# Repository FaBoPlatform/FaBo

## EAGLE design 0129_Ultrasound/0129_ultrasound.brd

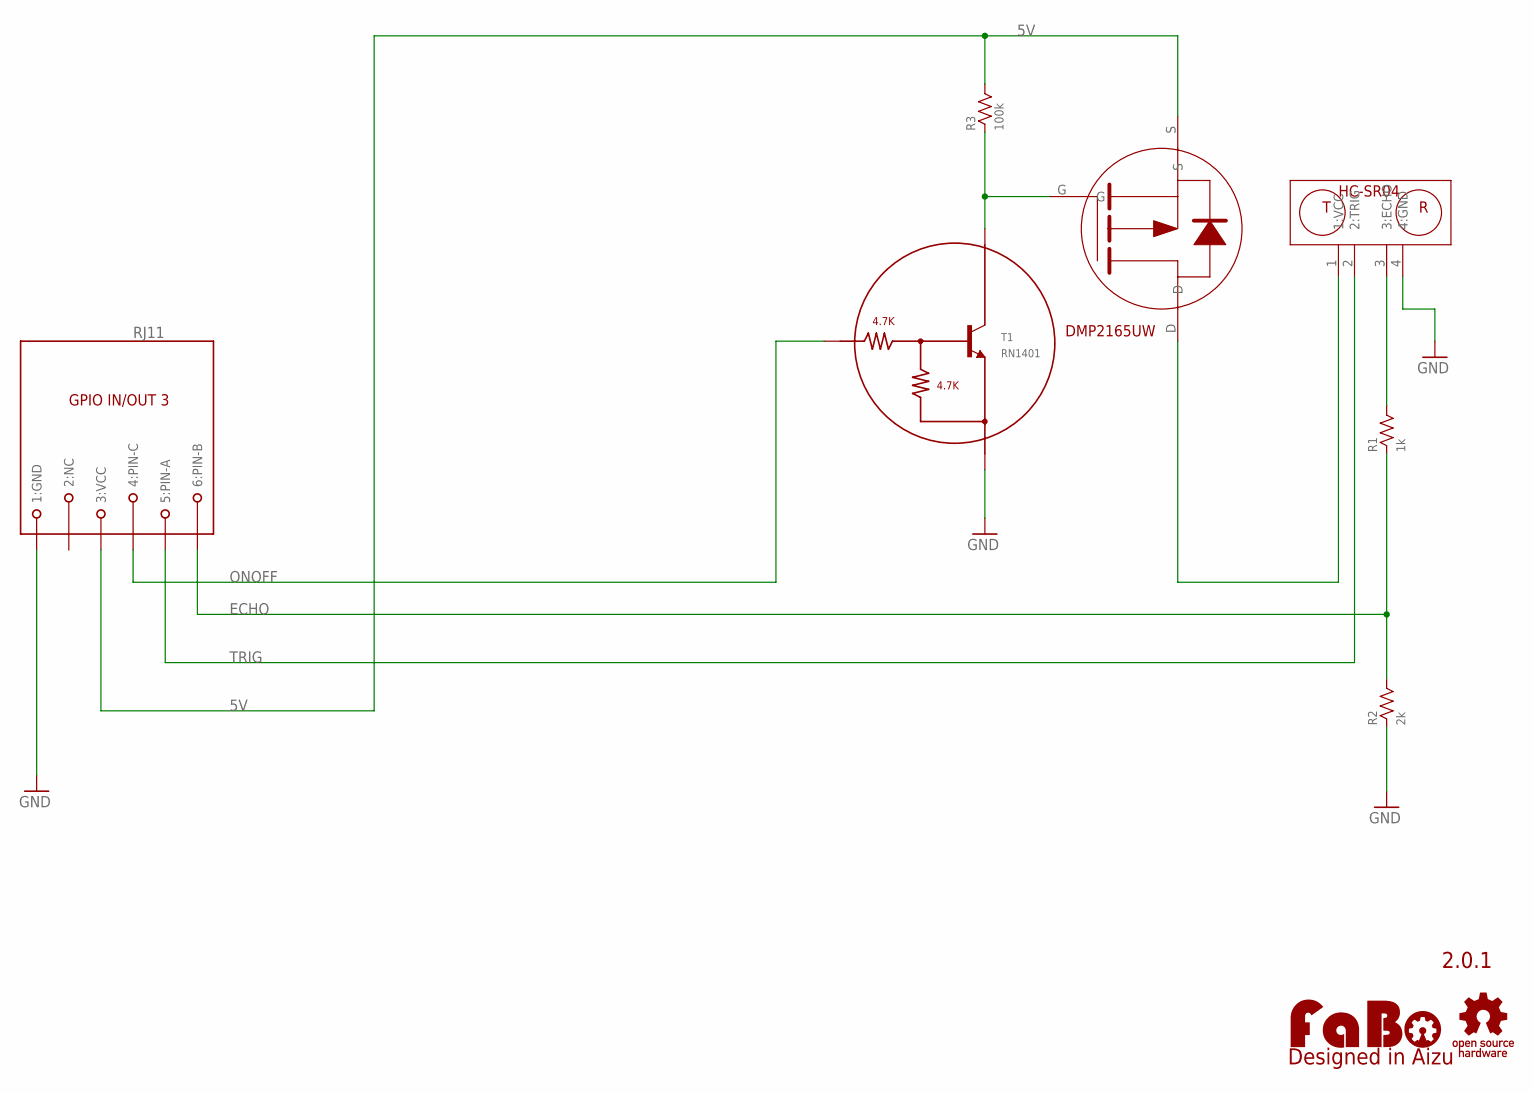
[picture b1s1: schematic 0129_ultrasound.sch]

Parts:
LOGO1: LOGO_FABO-M_BOTTOM; LOGO_FABO_M_BOTTOM
PFET: DMP2165UW; DMP2165_SOT323
R1: 1k; 0603-NARROW
R2: 2k; 0603-NARROW
R3: 100k; 0603-NARROW
RJ11: MODULAR-JACK-6P-RJ11_GPIO3; 7002-6PXC-X
T1: RN1401; SC-59
U$3: LOGO_OSHW-M_BOTTOM; LOGO_OSHW_M_BOTTOM
U$5: HC-SR04

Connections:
5V: PFET.S, R3.2, RJ11.3 (3:VCC)
ECHO: R1.1, R2.2, RJ11.6 (6:PIN-B)
GND: R2.1, RJ11.1 (1:GND), T1.E, U$5.4 (4:GND)
unnamed: R1.2, U$5.3 (3:ECHO)
unnamed: PFET.D, U$5.1 (1:VCC)
ONOFF: RJ11.4 (4:PIN-C), T1.B
POWERONOFF: PFET.G, R3.1, T1.C
TRIG: RJ11.5 (5:PIN-A), U$5.2 (2:TRIG)

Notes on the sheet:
2.0.1

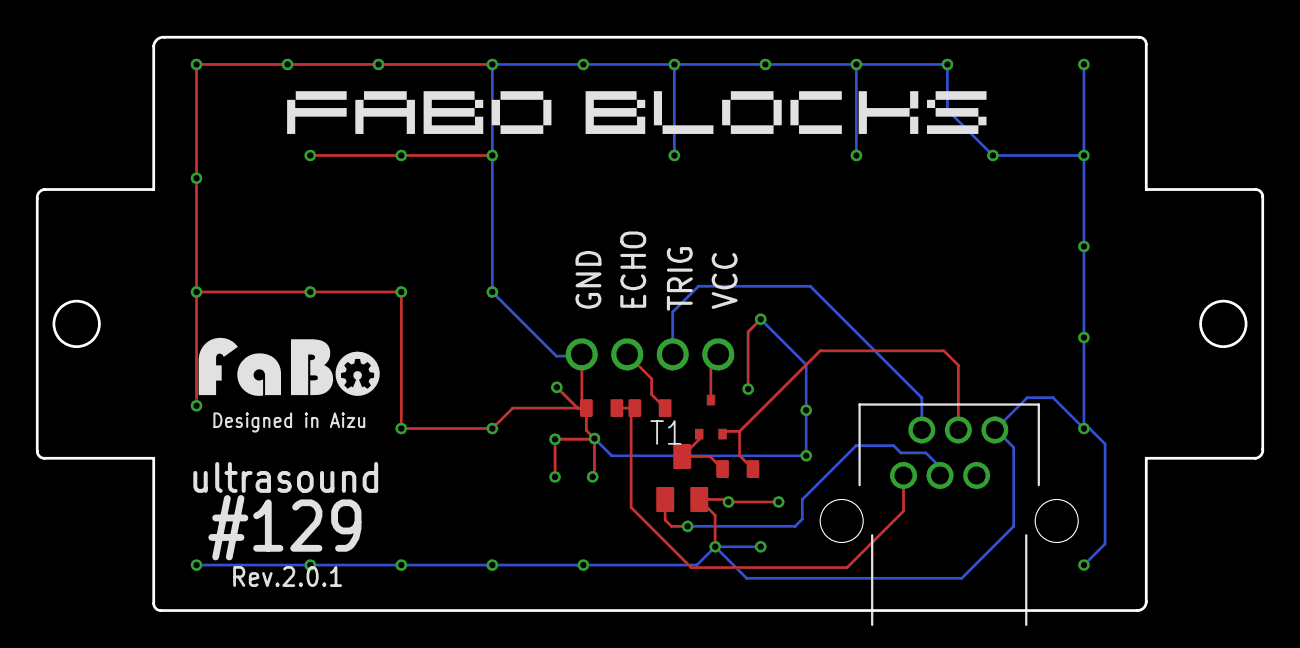
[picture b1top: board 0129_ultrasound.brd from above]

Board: 2 copper layers, 68.4 x 32.0 mm, 11 parts (1 on the bottom side), 8 nets.

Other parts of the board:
U$2, U$4: 4-1BLOCK

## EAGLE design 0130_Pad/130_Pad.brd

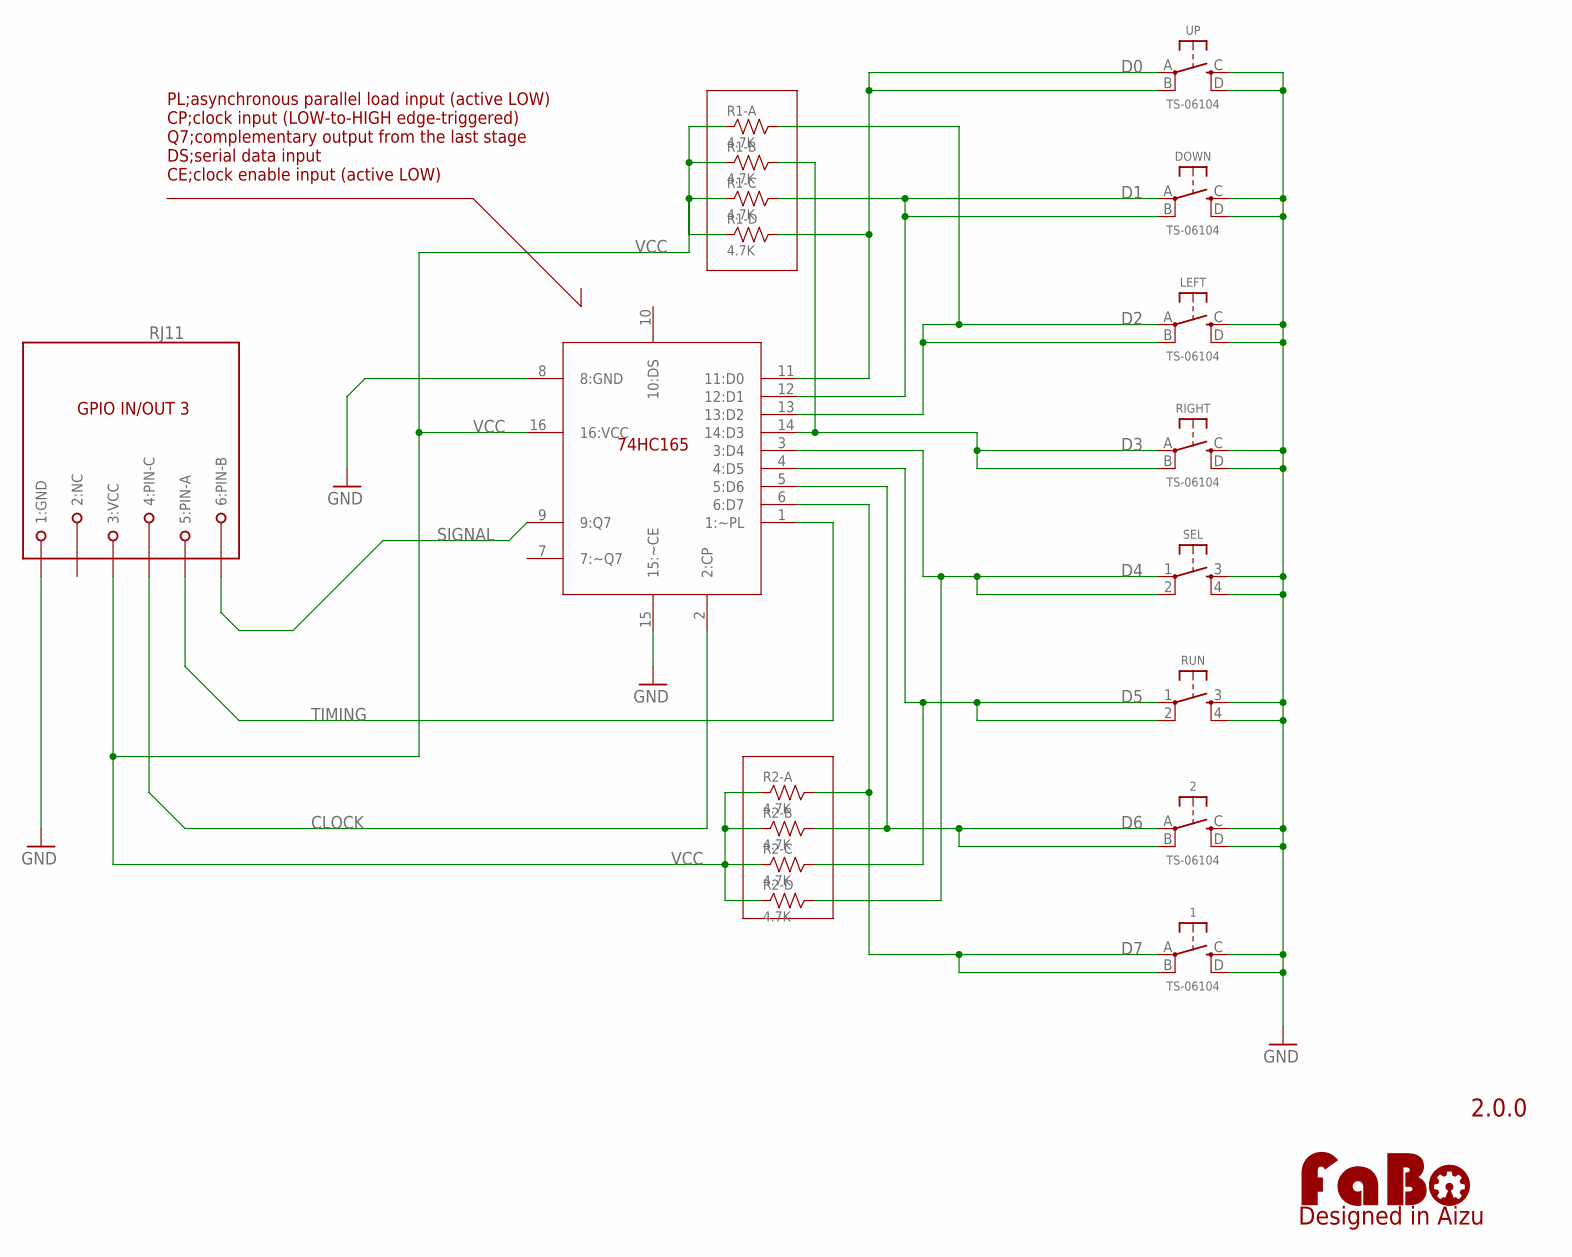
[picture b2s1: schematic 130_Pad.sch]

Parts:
1, 2: TS-06104
DOWN: TS-06104
LEFT: TS-06104
LOGO1: LOGO_FABO-M_BOTTOM; LOGO_FABO_M_BOTTOM
R1, R2: 4.7K; EXBV8V
RIGHT: TS-06104
RJ11: MODULAR-JACK-6P-RJ11_GPIO3; 7002-6PXC-X
RUN: TACT-SWITCH-SMD_KMR2; KMR2
SEL: TACT-SWITCH-SMD_KMR2; KMR2
U$5: 74HC165; SO16
UP: TS-06104

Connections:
CLOCK: RJ11.4 (4:PIN-C), U$5.2 (2:CP)
D0: R1.5 (2), U$5.11 (11:D0), UP.A, UP.B
D1: DOWN.A, DOWN.B, R1.6 (2), U$5.12 (12:D1)
D2: LEFT.A, LEFT.B, R1.8 (2), U$5.13 (13:D2)
D3: R1.7 (2), RIGHT.A, RIGHT.B, U$5.14 (14:D3)
D4: R2.5 (2), SEL.1, SEL.2, U$5.3 (3:D4)
D5: R2.6 (2), RUN.1, RUN.2, U$5.4 (4:D5)
D6: 2.A, 2.B, R2.7 (2), U$5.5 (5:D6)
D7: 1.A, 1.B, R2.8 (2), U$5.6 (6:D7)
GND: 1.C, 1.D, 2.C, 2.D, DOWN.C, DOWN.D, LEFT.C, LEFT.D, RIGHT.C, RIGHT.D, RJ11.1 (1:GND), RUN.3, RUN.4, SEL.3, SEL.4, U$5.8 (8:GND), U$5.15 (15:~CE), UP.C, UP.D
SIGNAL: RJ11.6 (6:PIN-B), U$5.9 (9:Q7)
TIMING: RJ11.5 (5:PIN-A), U$5.1 (1:~PL)
VCC: R1.1, R1.2 (1), R1.3 (1), R1.4 (1), R2.1, R2.2 (1), R2.3 (1), R2.4 (1), RJ11.3 (3:VCC), U$5.16 (16:VCC)

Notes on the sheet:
2.0.0
PL;asynchronous parallel load input (active LOW) CP;clock input (LOW-to-HIGH edge-triggered) Q7;complementary output from the last stage DS;serial data input CE;clock enable input (active LOW)

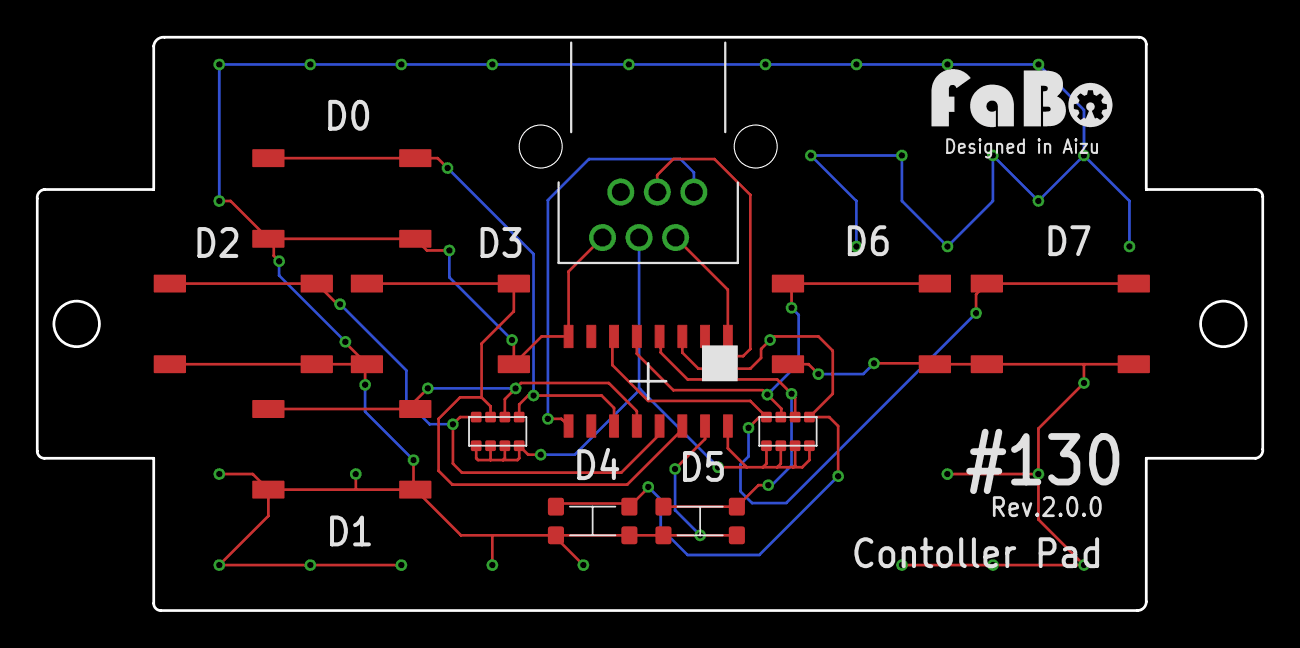
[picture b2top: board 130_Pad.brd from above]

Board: 2 copper layers, 68.4 x 32.0 mm, 15 parts (1 on the bottom side), 13 nets.

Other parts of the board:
U$2, U$4: 4-1BLOCK

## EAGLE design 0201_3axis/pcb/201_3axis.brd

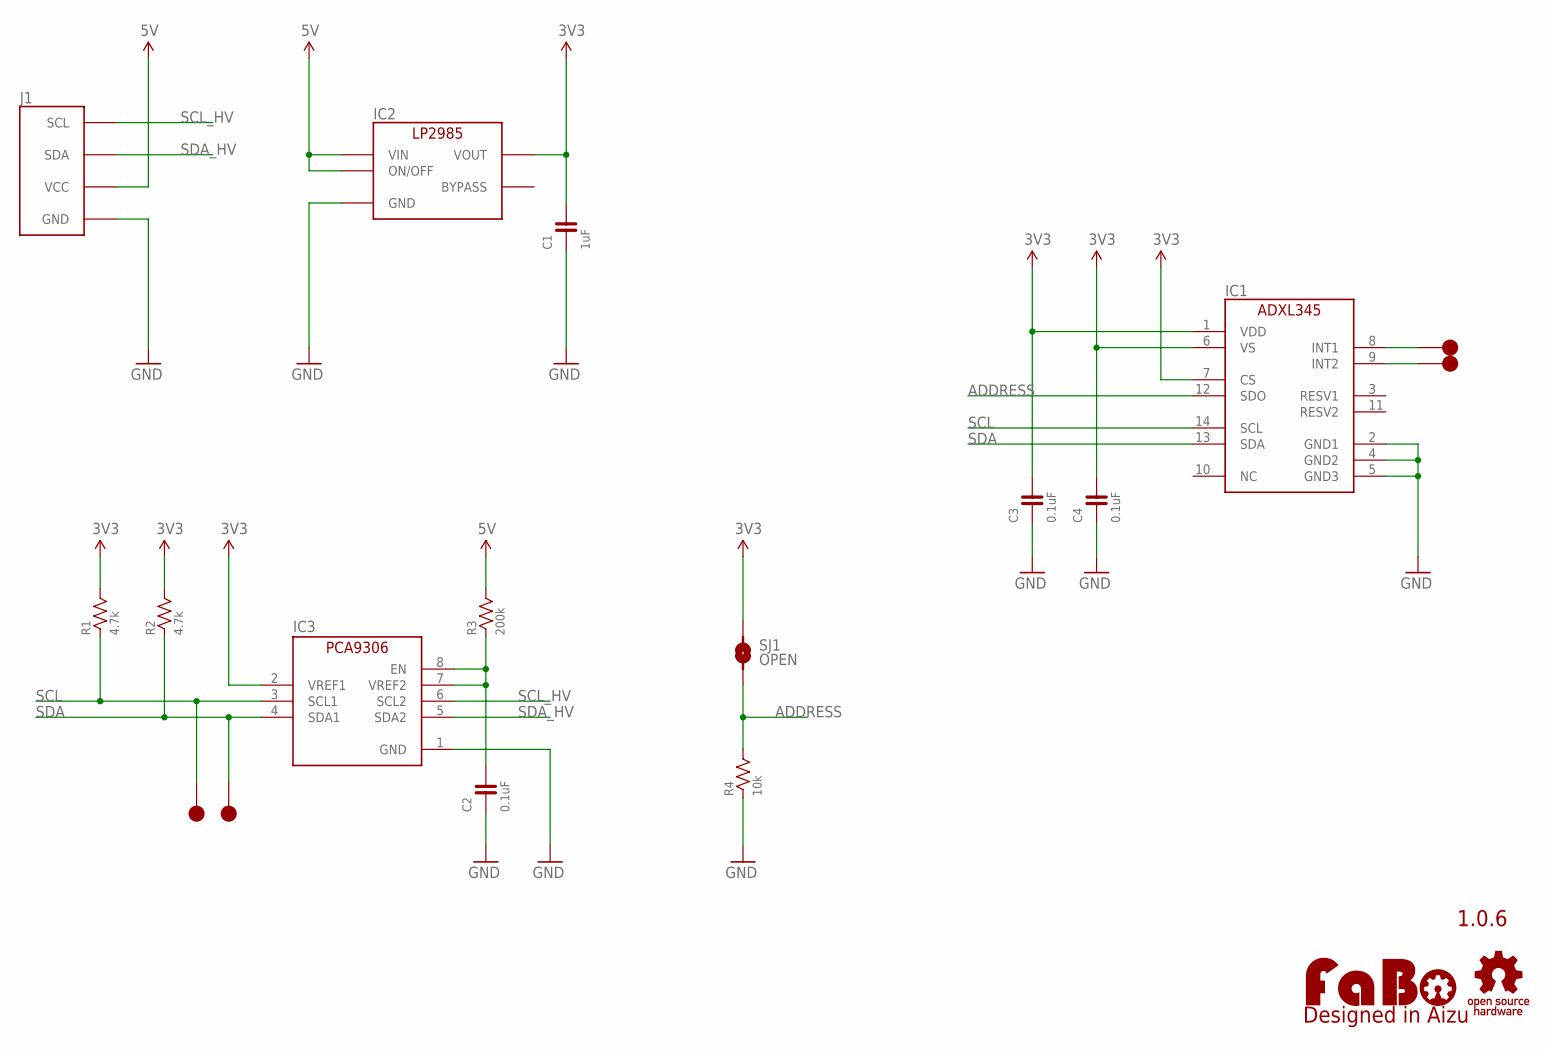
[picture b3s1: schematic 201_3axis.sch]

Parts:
C1: 1uF; 0603
C2, C3, C4: 0.1uF; 0603
IC1: AD-ADXL345; ANALOGDEVICES-ADXL345
IC2: LP2985-33DBV; SOT-23-5
IC3: PCA9306GM; XQFN8
J1: FABO_BRICK_I2C
LOGO1: LOGO_FABO-M; LOGO_FABO_M
R1, R2: 4.7k; 0603
R3: 200k; 0603
R4: 10k; 0603
SJ1: OPEN; SMD-JUMPER-2
TP1, TP2, TP3, TP4: TP-15
U$2: LOGO_OSHW-M_BOTTOM; LOGO_OSHW_M_BOTTOM

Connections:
3V3: C1.2, C3.2, C4.2, IC1.1 (VDD), IC1.6 (VS), IC1.7 (CS), IC2.5 (VOUT), IC3.2 (VREF1), R1.2, R2.2, SJ1.1
5V: IC2.1 (VIN), IC2.3 (ON/OFF), J1.VCC, R3.2
ADDRESS: IC1.12 (SDO), R4.2, SJ1.2
GND: C1.1, C2.1, C3.1, C4.1, IC1.2 (GND1), IC1.4 (GND2), IC1.5 (GND3), IC2.2 (GND), IC3.1 (GND), J1.GND, R4.1
unnamed: C2.2, IC3.7 (VREF2), IC3.8 (EN), R3.1
unnamed: IC1.8 (INT1), TP3.1
unnamed: IC1.9 (INT2), TP4.1
SCL: IC1.14 (SCL), IC3.3 (SCL1), R1.1, TP2.1
SCL_HV: IC3.6 (SCL2), J1.SCL
SDA: IC1.13 (SDA), IC3.4 (SDA1), R2.1, TP1.1
SDA_HV: IC3.5 (SDA2), J1.SDA

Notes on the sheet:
1.0.6

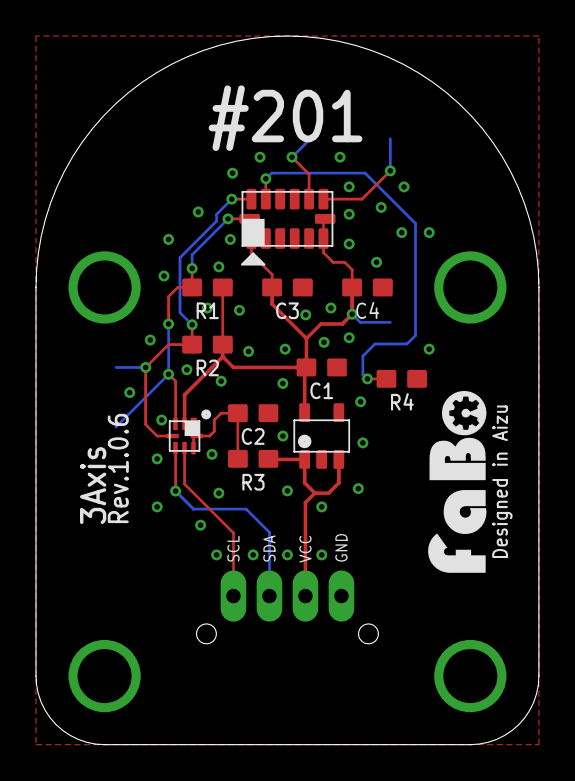
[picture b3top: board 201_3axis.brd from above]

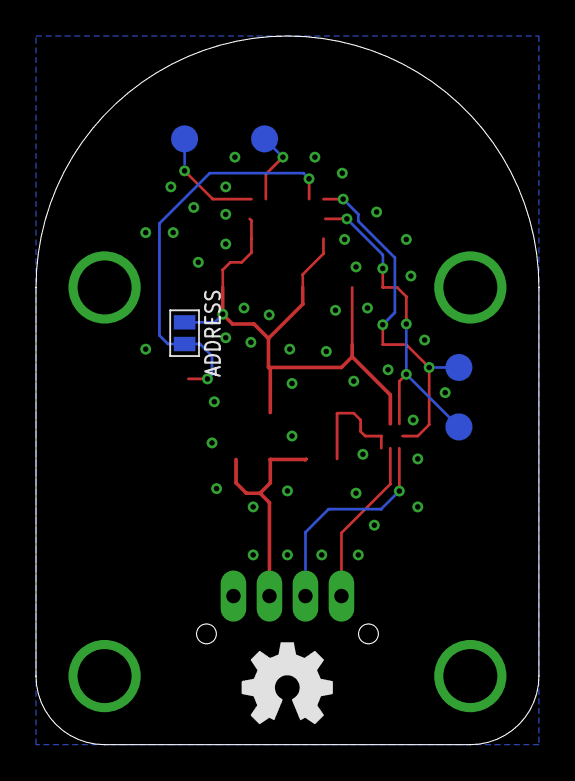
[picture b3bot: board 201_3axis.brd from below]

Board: 2 copper layers, 27.9 x 39.4 mm, 19 parts (5 on the bottom side), 11 nets.

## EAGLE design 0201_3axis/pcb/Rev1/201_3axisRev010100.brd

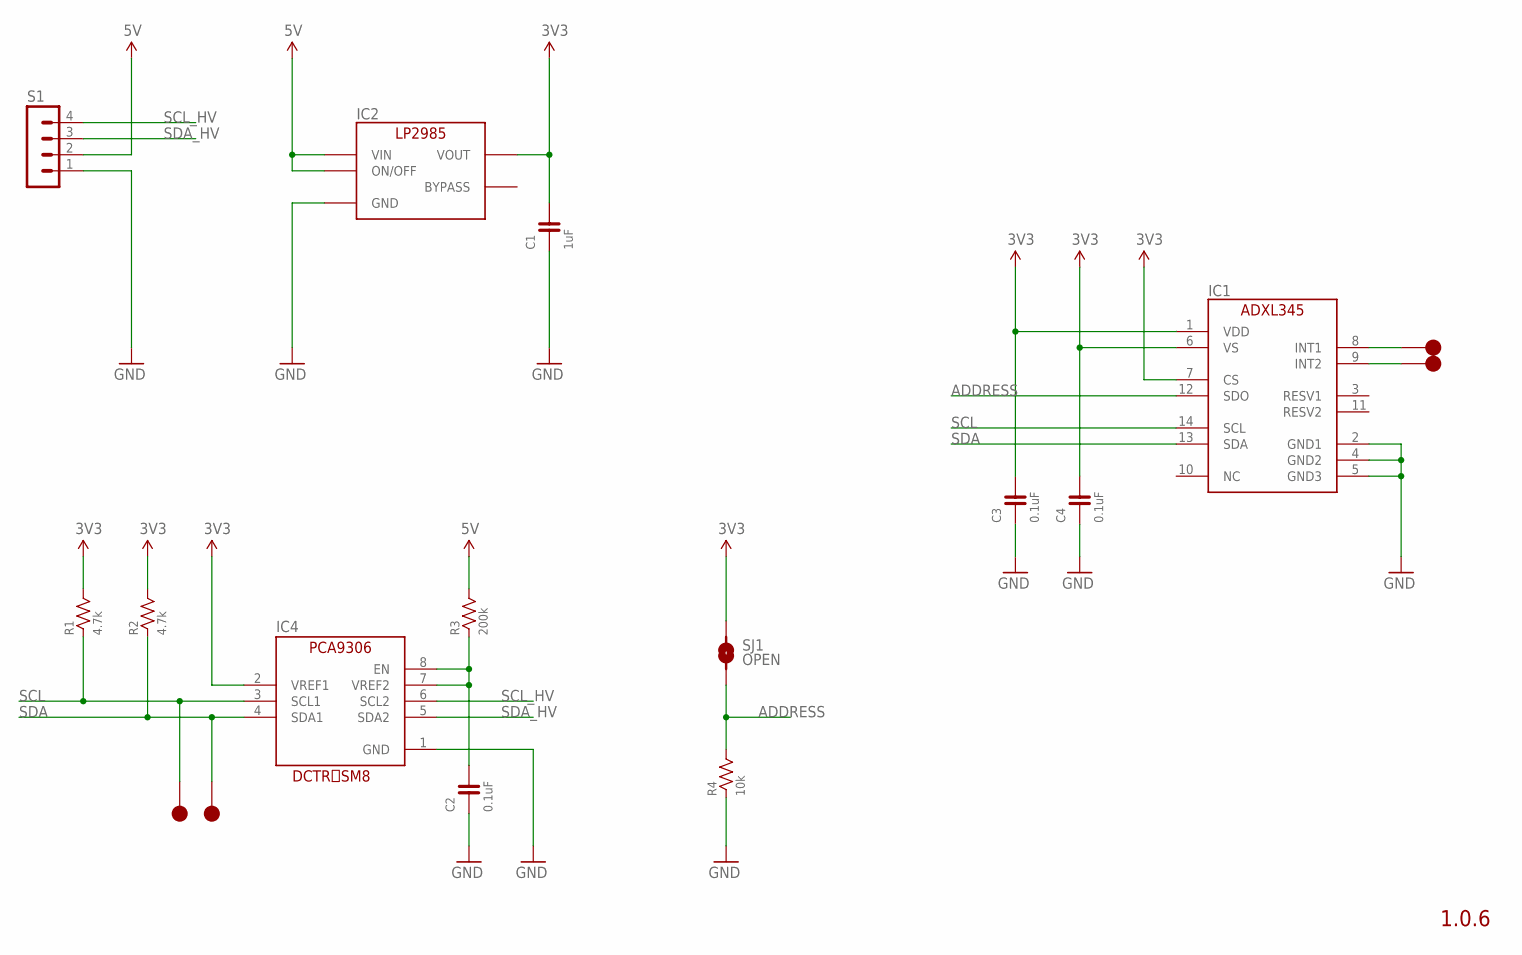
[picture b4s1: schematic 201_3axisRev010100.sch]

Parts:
C1: 1uF; 0603
C2, C3, C4: 0.1uF; 0603
IC1: AD-ADXL345; ANALOGDEVICES-ADXL345
IC2: LP2985-33DBV; SOT-23-5
IC4: PCA9306_SSOP; 8PIN-SSOP
R1, R2: 4.7k; 0603
R3: 200k; 0603
R4: 10k; 0603
S1: MA04-1
SJ1: OPEN; SMD-JUMPER-2
TP1, TP2, TP3, TP4: TP-15

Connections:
3V3: C1.2, C3.2, C4.2, IC1.1 (VDD), IC1.6 (VS), IC1.7 (CS), IC2.5 (VOUT), IC4.2 (VREF1), R1.2, R2.2, SJ1.1
5V: IC2.1 (VIN), IC2.3 (ON/OFF), R3.2, S1.2
ADDRESS: IC1.12 (SDO), R4.2, SJ1.2
GND: C1.1, C2.1, C3.1, C4.1, IC1.2 (GND1), IC1.4 (GND2), IC1.5 (GND3), IC2.2 (GND), IC4.1 (GND), R4.1, S1.1
INT1: IC1.8 (INT1), TP3.1
INT2: IC1.9 (INT2), TP4.1
unnamed: C2.2, IC4.7 (VREF2), IC4.8 (EN), R3.1
SCL: IC1.14 (SCL), IC4.3 (SCL1), R1.1, TP2.1
SCL_HV: IC4.6 (SCL2), S1.4
SDA: IC1.13 (SDA), IC4.4 (SDA1), R2.1, TP1.1
SDA_HV: IC4.5 (SDA2), S1.3

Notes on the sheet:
1.0.6
DCTR SM8

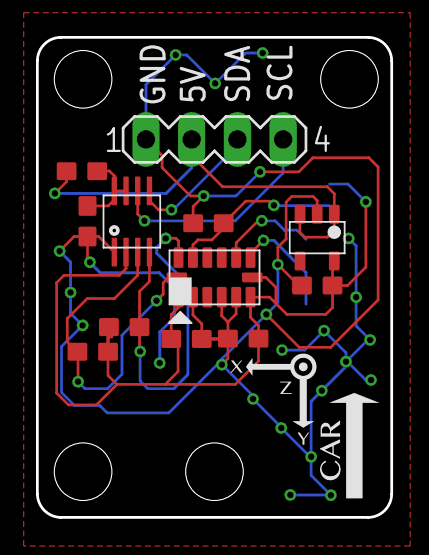
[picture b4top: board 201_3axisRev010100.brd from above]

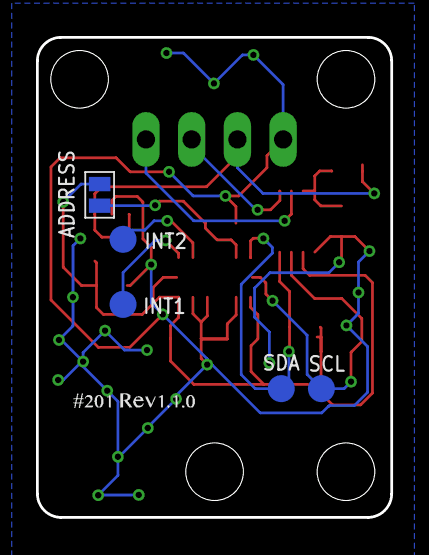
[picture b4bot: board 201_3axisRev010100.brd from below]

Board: 2 copper layers, 19.7 x 26.7 mm, 17 parts (5 on the bottom side), 11 nets.

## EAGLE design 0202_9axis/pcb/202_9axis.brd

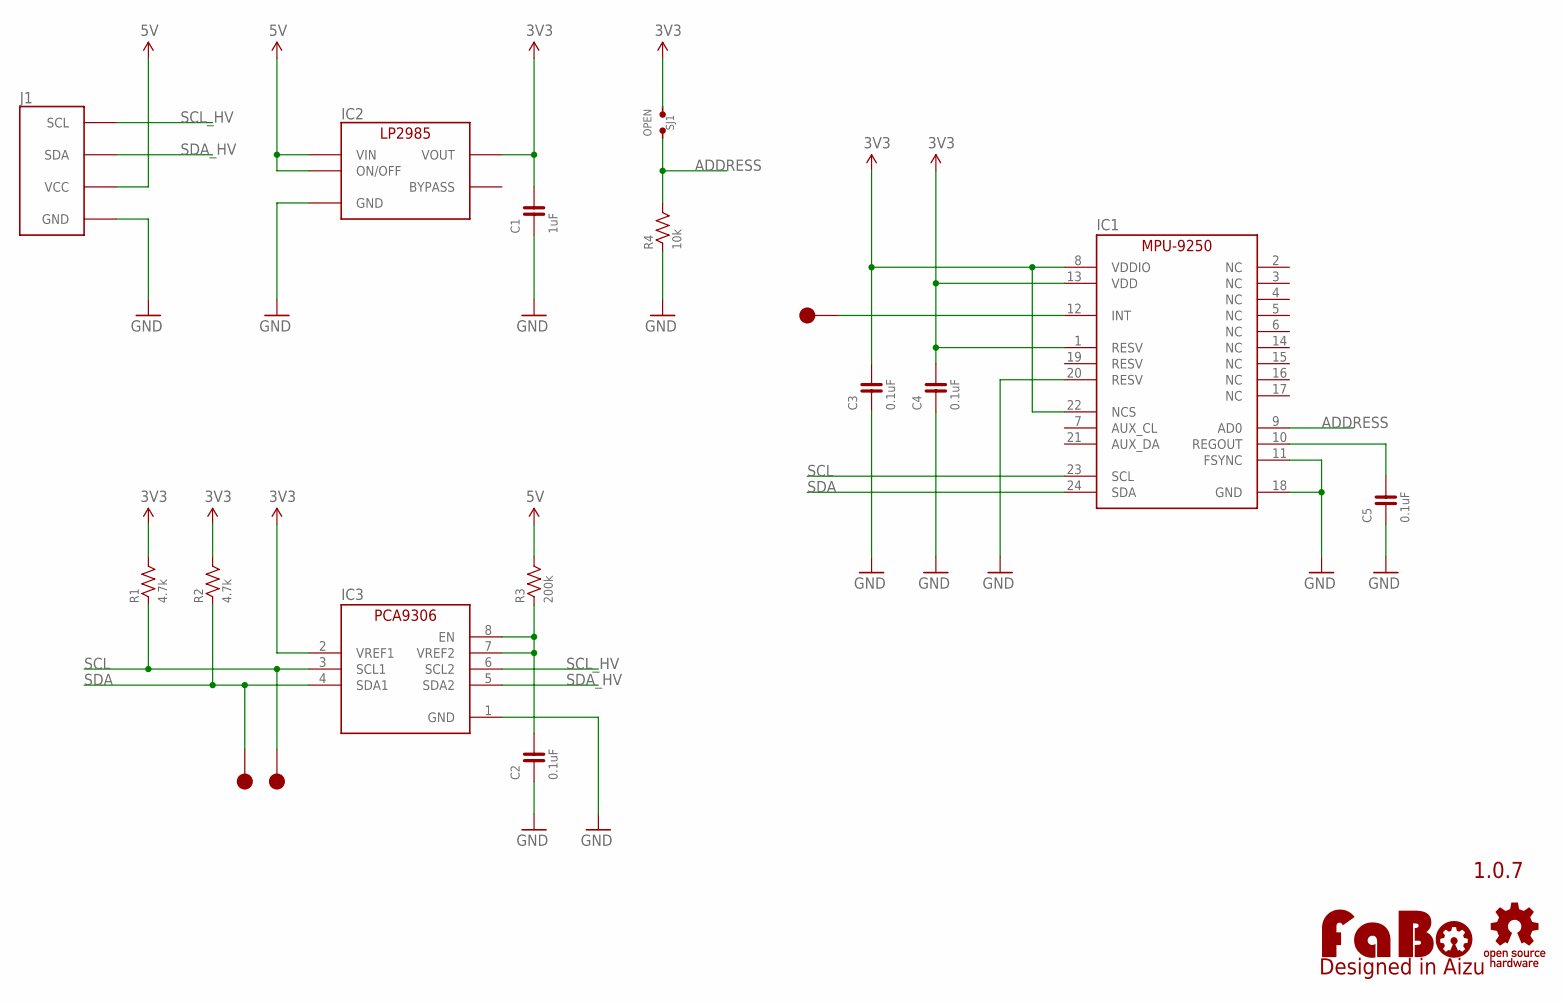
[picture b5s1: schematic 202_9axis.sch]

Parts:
C1: 1uF; 0603
C2, C3, C4, C5: 0.1uF; 0603
IC1: IS-MPU9250; INVENSENSE-MPU9250
IC2: LP2985-33DBV; SOT-23-5
IC3: PCA9306GM; XQFN8
J1: FABO_BRICK_I2C
LOGO1: LOGO_FABO-M; LOGO_FABO_M
R1, R2: 4.7k; 0603
R3: 200k; 0603
R4: 10k; 0603
SJ1: OPEN; SMD-JUMPER-2-OPEN
TP1, TP2, TP3: TP-15
U$2: LOGO_OSHW-M_BOTTOM; LOGO_OSHW_M_BOTTOM

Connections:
3V3: C1.2, C3.2, C4.2, IC1.1 (RESV), IC1.8 (VDDIO), IC1.13 (VDD), IC1.22 (NCS), IC2.5 (VOUT), IC3.2 (VREF1), R1.2, R2.2, SJ1.1
5V: IC2.1 (VIN), IC2.3 (ON/OFF), J1.VCC, R3.2
ADDRESS: IC1.9 (AD0), R4.2, SJ1.2
GND: C1.1, C2.1, C3.1, C4.1, C5.1, IC1.11 (FSYNC), IC1.18 (GND), IC1.20 (RESV), IC2.2 (GND), IC3.1 (GND), J1.GND, R4.1
unnamed: C2.2, IC3.7 (VREF2), IC3.8 (EN), R3.1
unnamed: IC1.12 (INT), TP3.1
REGOUT: C5.2, IC1.10 (REGOUT)
SCL: IC1.23 (SCL), IC3.3 (SCL1), R1.1, TP2.1
SCL_HV: IC3.6 (SCL2), J1.SCL
SDA: IC1.24 (SDA), IC3.4 (SDA1), R2.1, TP1.1
SDA_HV: IC3.5 (SDA2), J1.SDA

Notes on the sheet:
1.0.7

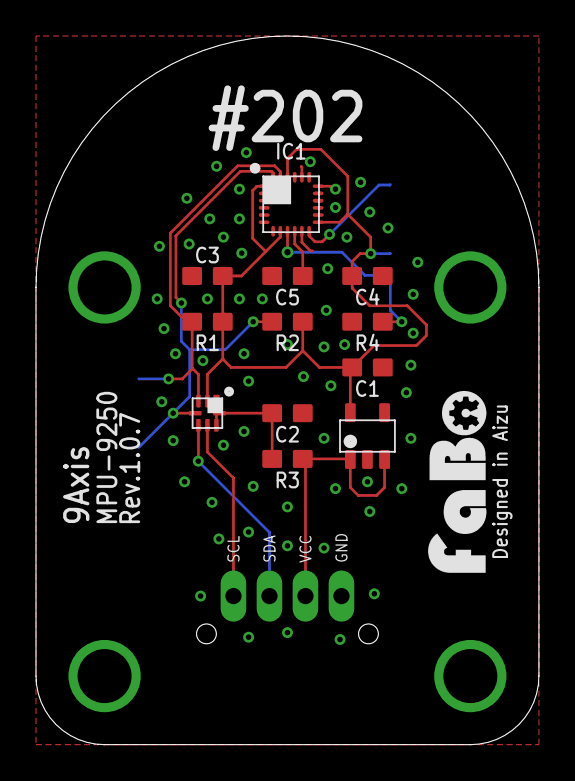
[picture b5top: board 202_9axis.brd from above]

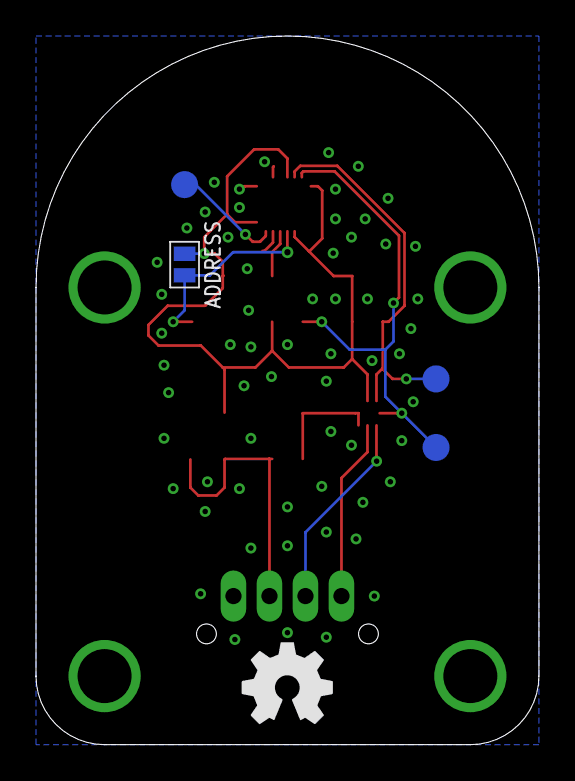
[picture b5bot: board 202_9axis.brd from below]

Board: 2 copper layers, 27.9 x 39.4 mm, 19 parts (4 on the bottom side), 11 nets.

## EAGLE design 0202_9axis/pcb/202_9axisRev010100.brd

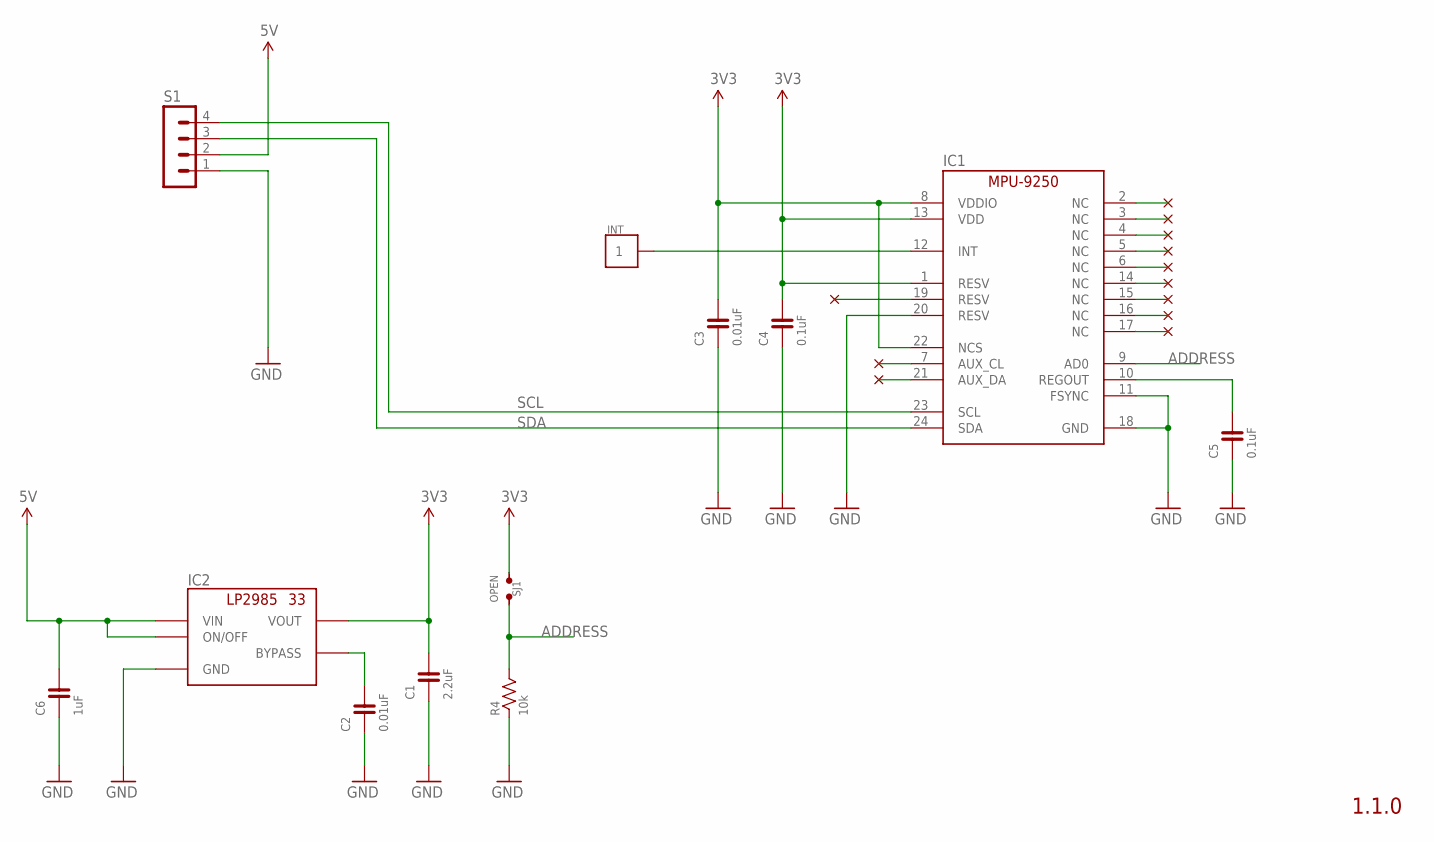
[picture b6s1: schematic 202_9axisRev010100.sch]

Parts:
C1: 2.2uF; 0603
C2, C3: 0.01uF; 0603
C4, C5: 0.1uF; 0603
C6: 1uF; 0603
IC1: IS-MPU9250; INVENSENSE-MPU9250
IC2: LP2985-33DBV; SOT-23-5
INT: PIN_1X1
R4: 10k; 0603
S1: MA04-1
SJ1: OPEN; SMD-JUMPER-2-OPEN

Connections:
3V3: C1.2, C3.2, C4.2, IC1.1 (RESV), IC1.8 (VDDIO), IC1.13 (VDD), IC1.22 (NCS), IC2.5 (VOUT), SJ1.1
5V: C6.2, IC2.1 (VIN), IC2.3 (ON/OFF), S1.2
ADDRESS: IC1.9 (AD0), R4.2, SJ1.2
GND: C1.1, C2.1, C3.1, C4.1, C5.1, C6.1, IC1.11 (FSYNC), IC1.18 (GND), IC1.20 (RESV), IC2.2 (GND), R4.1, S1.1
unnamed: C2.2, IC2.4 (BYPASS)
unnamed: IC1.12 (INT), INT.1
REGOUT: C5.2, IC1.10 (REGOUT)
SCL: IC1.23 (SCL), S1.4
SDA: IC1.24 (SDA), S1.3

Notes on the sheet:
1.1.0

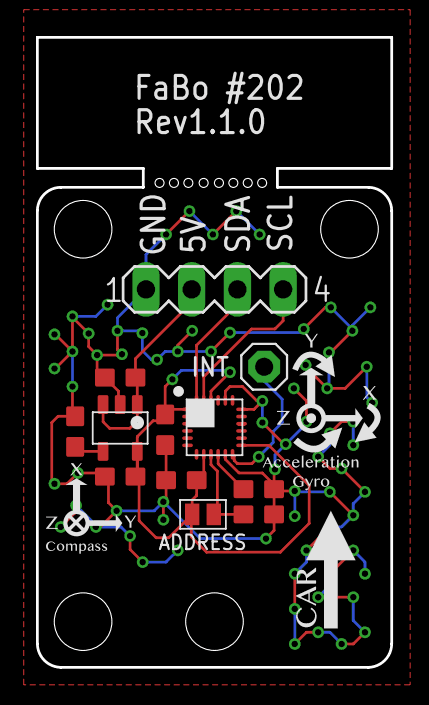
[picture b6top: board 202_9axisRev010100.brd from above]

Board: 2 copper layers, 19.7 x 35.0 mm, 13 parts (0 on the bottom side), 9 nets.

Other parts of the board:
U$2: LOGO_FABO_S_BOTTOM

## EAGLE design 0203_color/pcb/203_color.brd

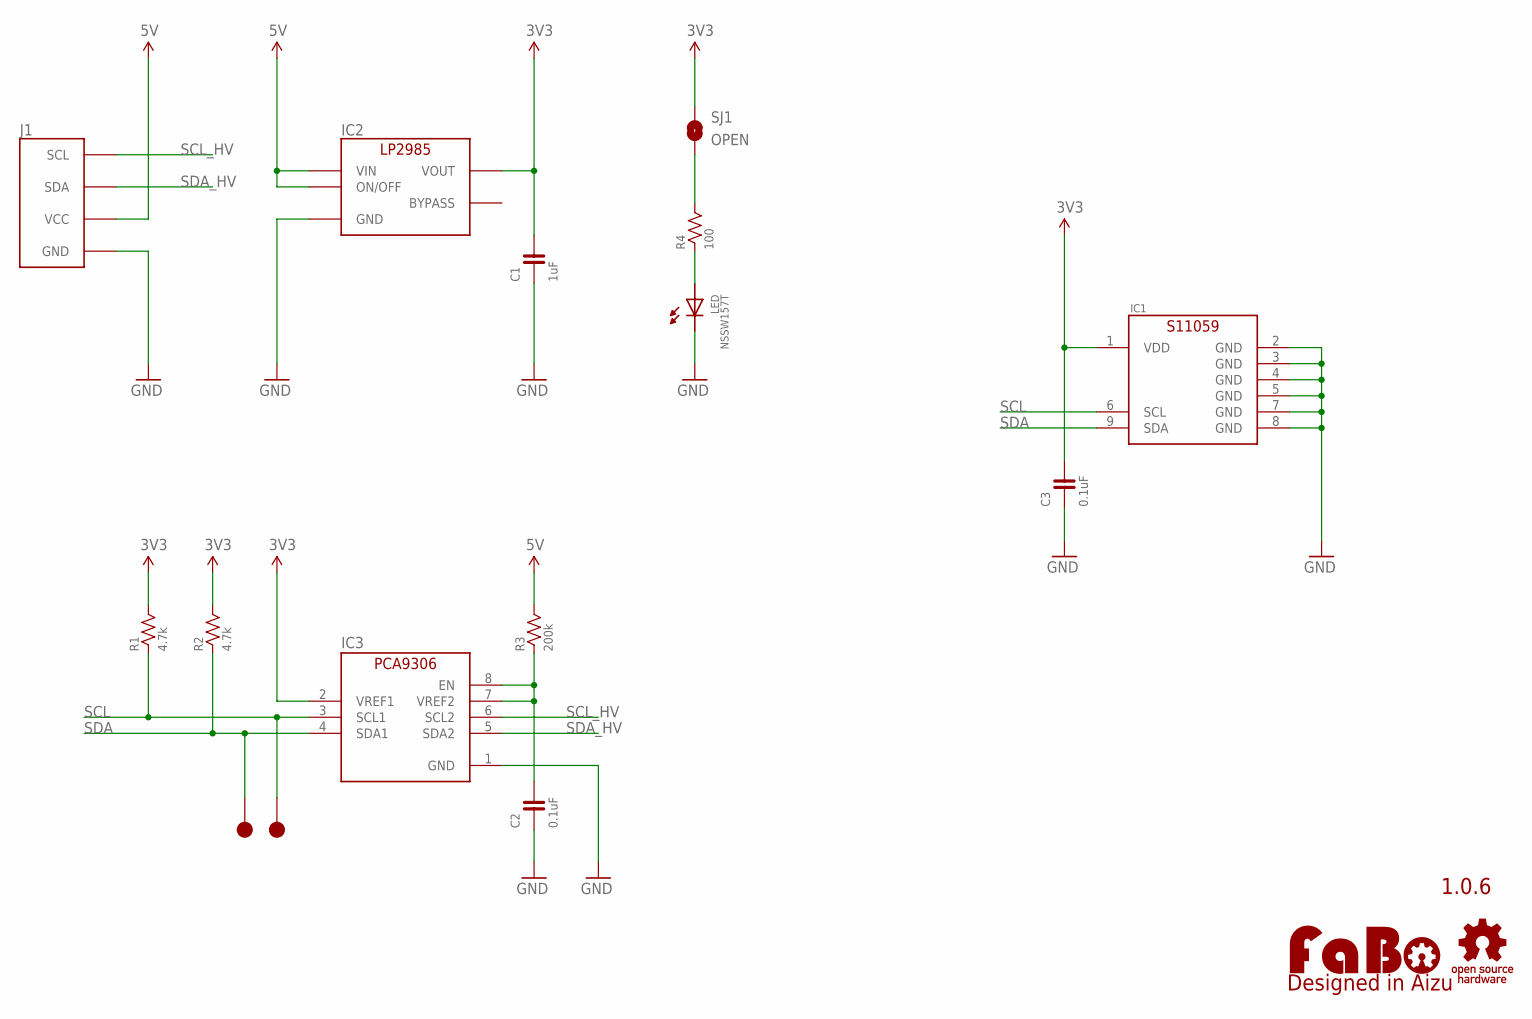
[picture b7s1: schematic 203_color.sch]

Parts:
C1: 1uF; 0603
C2, C3: 0.1uF; 0603
IC1: HAMAMATSU-S11059
IC2: LP2985-33DBV; SOT-23-5
IC3: PCA9306GM; XQFN8
J1: FABO_BRICK_I2C
LED: NSSW157T
LOGO1: LOGO_FABO-M; LOGO_FABO_M
R1, R2: 4.7k; 0603
R3: 200k; 0603
R4: 100; 0603
SJ1: OPEN; SMD-JUMPER-2-OPEN
TP1, TP2: TP-15
U$2: LOGO_OSHW-M_BOTTOM; LOGO_OSHW_M_BOTTOM

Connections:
3V3: C1.2, C3.2, IC1.1 (VDD), IC2.5 (VOUT), IC3.2 (VREF1), R1.2, R2.2, SJ1.1
5V: IC2.1 (VIN), IC2.3 (ON/OFF), J1.VCC, R3.2
GND: C1.1, C2.1, C3.1, IC1.2 (GND), IC1.3 (GND), IC1.4 (GND), IC1.5 (GND), IC1.7 (GND), IC1.8 (GND), IC2.2 (GND), IC3.1 (GND), J1.GND, LED.CATHODE1 (CATHODE), LED.CATHODE2 (CATHODE)
unnamed: LED.ANODE1 (ANODE), LED.ANODE2 (ANODE), R4.1
unnamed: C2.2, IC3.7 (VREF2), IC3.8 (EN), R3.1
unnamed: R4.2, SJ1.2
SCL: IC1.6 (SCL), IC3.3 (SCL1), R1.1, TP2.1
SCL_HV: IC3.6 (SCL2), J1.SCL
SDA: IC1.9 (SDA), IC3.4 (SDA1), R2.1, TP1.1
SDA_HV: IC3.5 (SDA2), J1.SDA

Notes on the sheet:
1.0.6

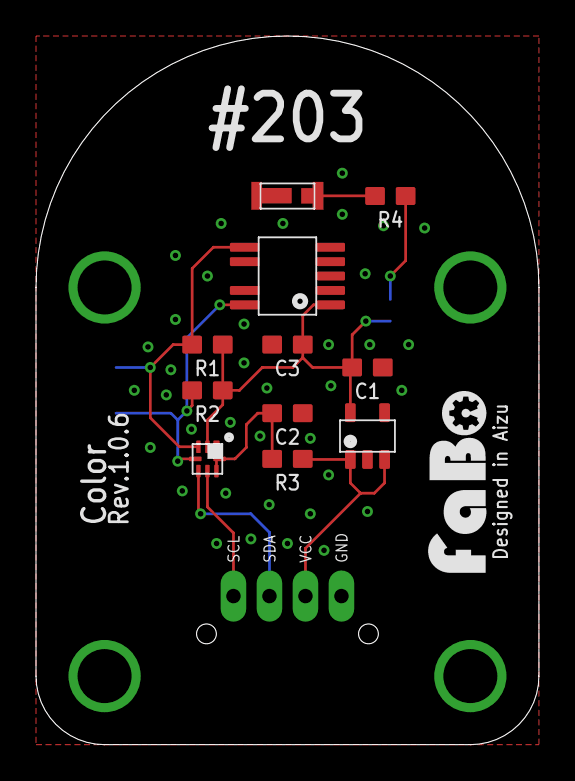
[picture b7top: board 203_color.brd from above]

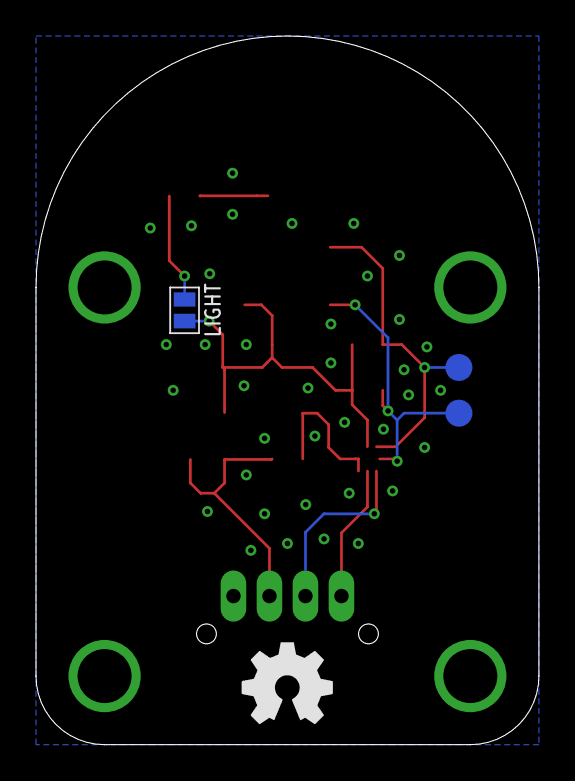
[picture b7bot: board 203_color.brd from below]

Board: 2 copper layers, 27.9 x 39.4 mm, 17 parts (3 on the bottom side), 10 nets.

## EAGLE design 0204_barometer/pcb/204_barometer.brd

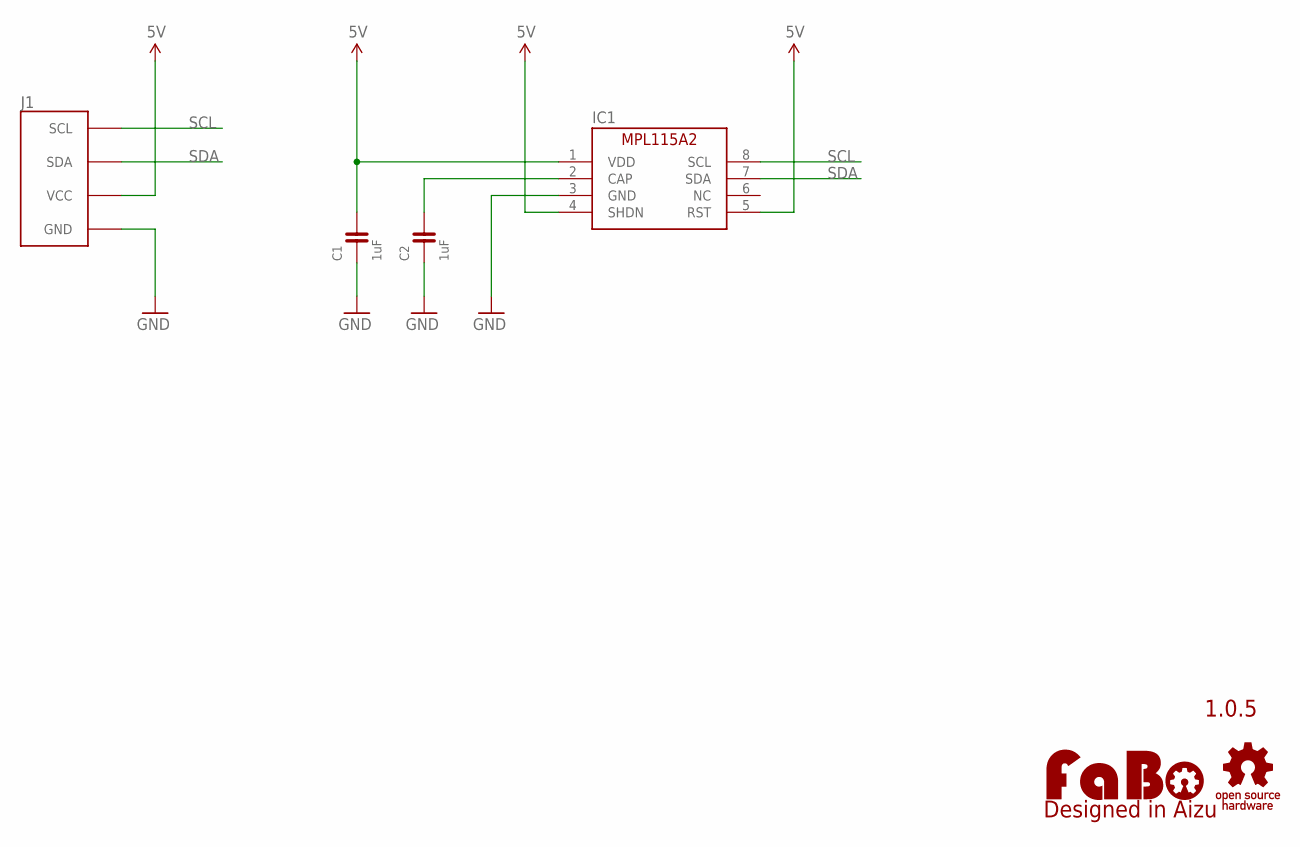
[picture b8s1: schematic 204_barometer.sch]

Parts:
C1, C2: 1uF; 0603
IC1: FS-MPL115A2; FREESCALE-MPL115A2
J1: FABO_BRICK_I2C
LOGO1: LOGO_FABO-M; LOGO_FABO_M
U$2: LOGO_OSHW-M_BOTTOM; LOGO_OSHW_M_BOTTOM

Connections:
5V: C1.2, IC1.1 (VDD), IC1.4 (SHDN), IC1.5 (RST), J1.VCC
GND: C1.1, C2.1, IC1.3 (GND), J1.GND
unnamed: C2.2, IC1.2 (CAP)
SCL: IC1.8 (SCL), J1.SCL
SDA: IC1.7 (SDA), J1.SDA

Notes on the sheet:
1.0.5

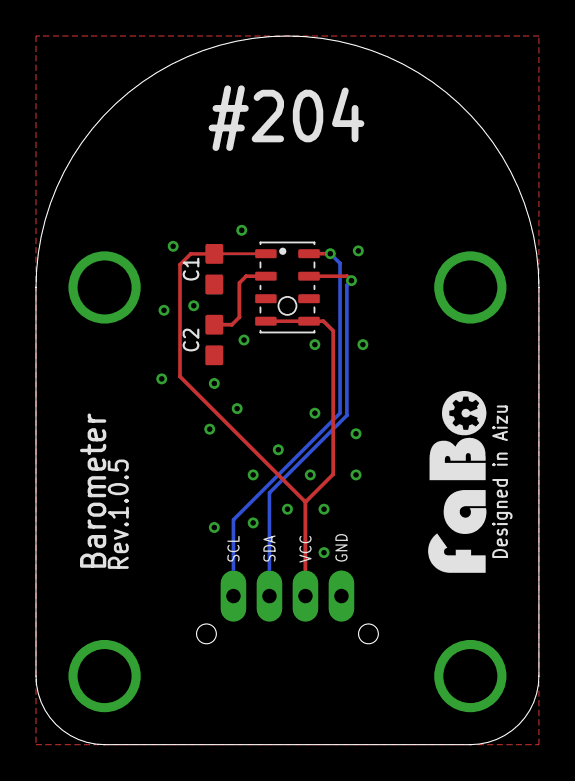
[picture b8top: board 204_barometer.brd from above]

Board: 2 copper layers, 27.9 x 39.4 mm, 6 parts (0 on the bottom side), 5 nets.

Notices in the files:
parts and their libraries:
FaBo-Resistors: Released under the Creative Commons Attribution-ShareAlike 4.0 License
https://creativecommons.org/licenses/by-sa/4.0
FaBo-etc: Released under the Creative Commons
